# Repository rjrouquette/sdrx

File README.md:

# sdrx
software defined receiver

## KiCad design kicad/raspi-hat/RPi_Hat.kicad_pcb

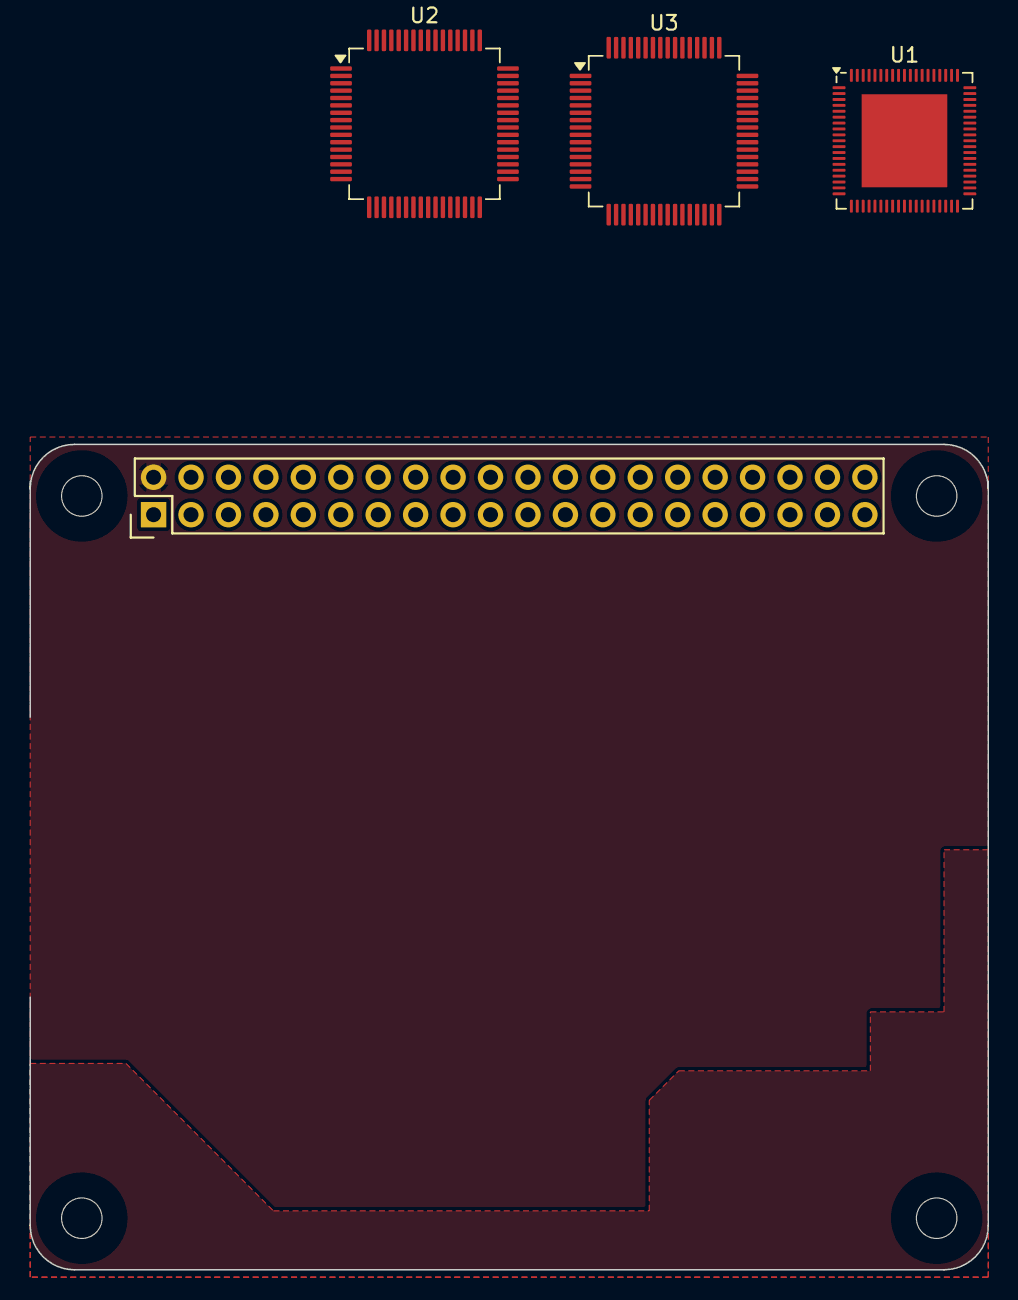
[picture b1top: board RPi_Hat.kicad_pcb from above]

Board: 2 copper layers, 65.0 x 56.0 mm, 4 parts (0 on the bottom side), 4 nets, no tracks yet.

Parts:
J2: RPi_GPIO; Pin_Header_Straight_2x20
U1: FT601Q; QFN-76-1EP_9x9mm_P0.4mm_EP5.81x6.31mm
U2, U3: SN74V245-7PAG; TQFP-64_10x10mm_P0.5mm

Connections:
GND: U1.1 (GND), U1.26 (GND), U1.29 (GND), U1.36 (GND), U1.77 (GND)
unnamed: U1.20 (VCC33), U1.24 (VCC33), U1.38 (VCC33)
unnamed: U1.14 (VCCIO), U1.49 (VCCIO), U1.59 (VCCIO), U1.68 (VCCIO)
unnamed: U1.3 (VD10), U1.30 (VD10), U1.33 (VD10), U1.48 (VD10)

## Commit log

2023-05-20 start sdrx project as clone of gpsdo
2023-05-20 restructuring code as PTP client
2023-05-21 increase sample window
2023-05-21 change hostname
2023-05-21 tuning PLL
2023-05-21 restructuring PTP client
2023-05-22 implementing drift calculation
2023-05-22 fix offset flapping on startup
2023-05-22 add ADC datasheet
2023-05-22 add FIFO datasheet
2023-05-22 fix delay estimation
2023-05-22 debugging PTP
2023-05-23 cleanup scheduler status
2023-05-23 fix flapping on startup
2023-05-23 reduce PTP startup time
2023-05-23 code cleanup
2023-05-23 cleanup run status
2023-05-25 cleanup scheduler code
2023-05-25 testing new scheduling paradigm
2023-05-25 fix bug in extended once tasks
2023-05-26 fix sign of offset rms and stddev on initial sample
2023-05-26 improve regression stability
2023-05-26 relax residual error threshold
2023-05-26 disable ADC hardware averaging
2023-05-26 enable ADC hardware averaging
2023-05-26 drain ADC fifo
2023-05-26 increase sample rate
2023-05-26 test use of ISR for temperature measurement
2023-05-26 tweak temperature measurement
2023-05-27 increase delay polling rate
2023-05-27 reduce scheduler memory footprint
2023-05-28 tweaking temperature measurement
2023-06-07 simplify scheduler
2023-06-11 update scheduler code
2023-06-11 reduce pll stats alpha
2023-06-11 increase time constant for temperature filtering
2023-06-13 soften offset PLL
2023-06-13 tighten offset PLL
2023-06-24 scale delay request interval with sync rate
2023-06-24 increase delay request rate
2023-06-24 dither delay request rate
2023-07-21 fix segfault on boot
2025-03-10 add receiver raspi-hat
2025-03-10 add datasheets
2025-03-10 update tm4c support
